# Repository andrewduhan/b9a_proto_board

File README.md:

# B9A Proto Board
Prototyping board for vacuum tubes that use a B9A socket

Board measures 3.95" x 3.15"

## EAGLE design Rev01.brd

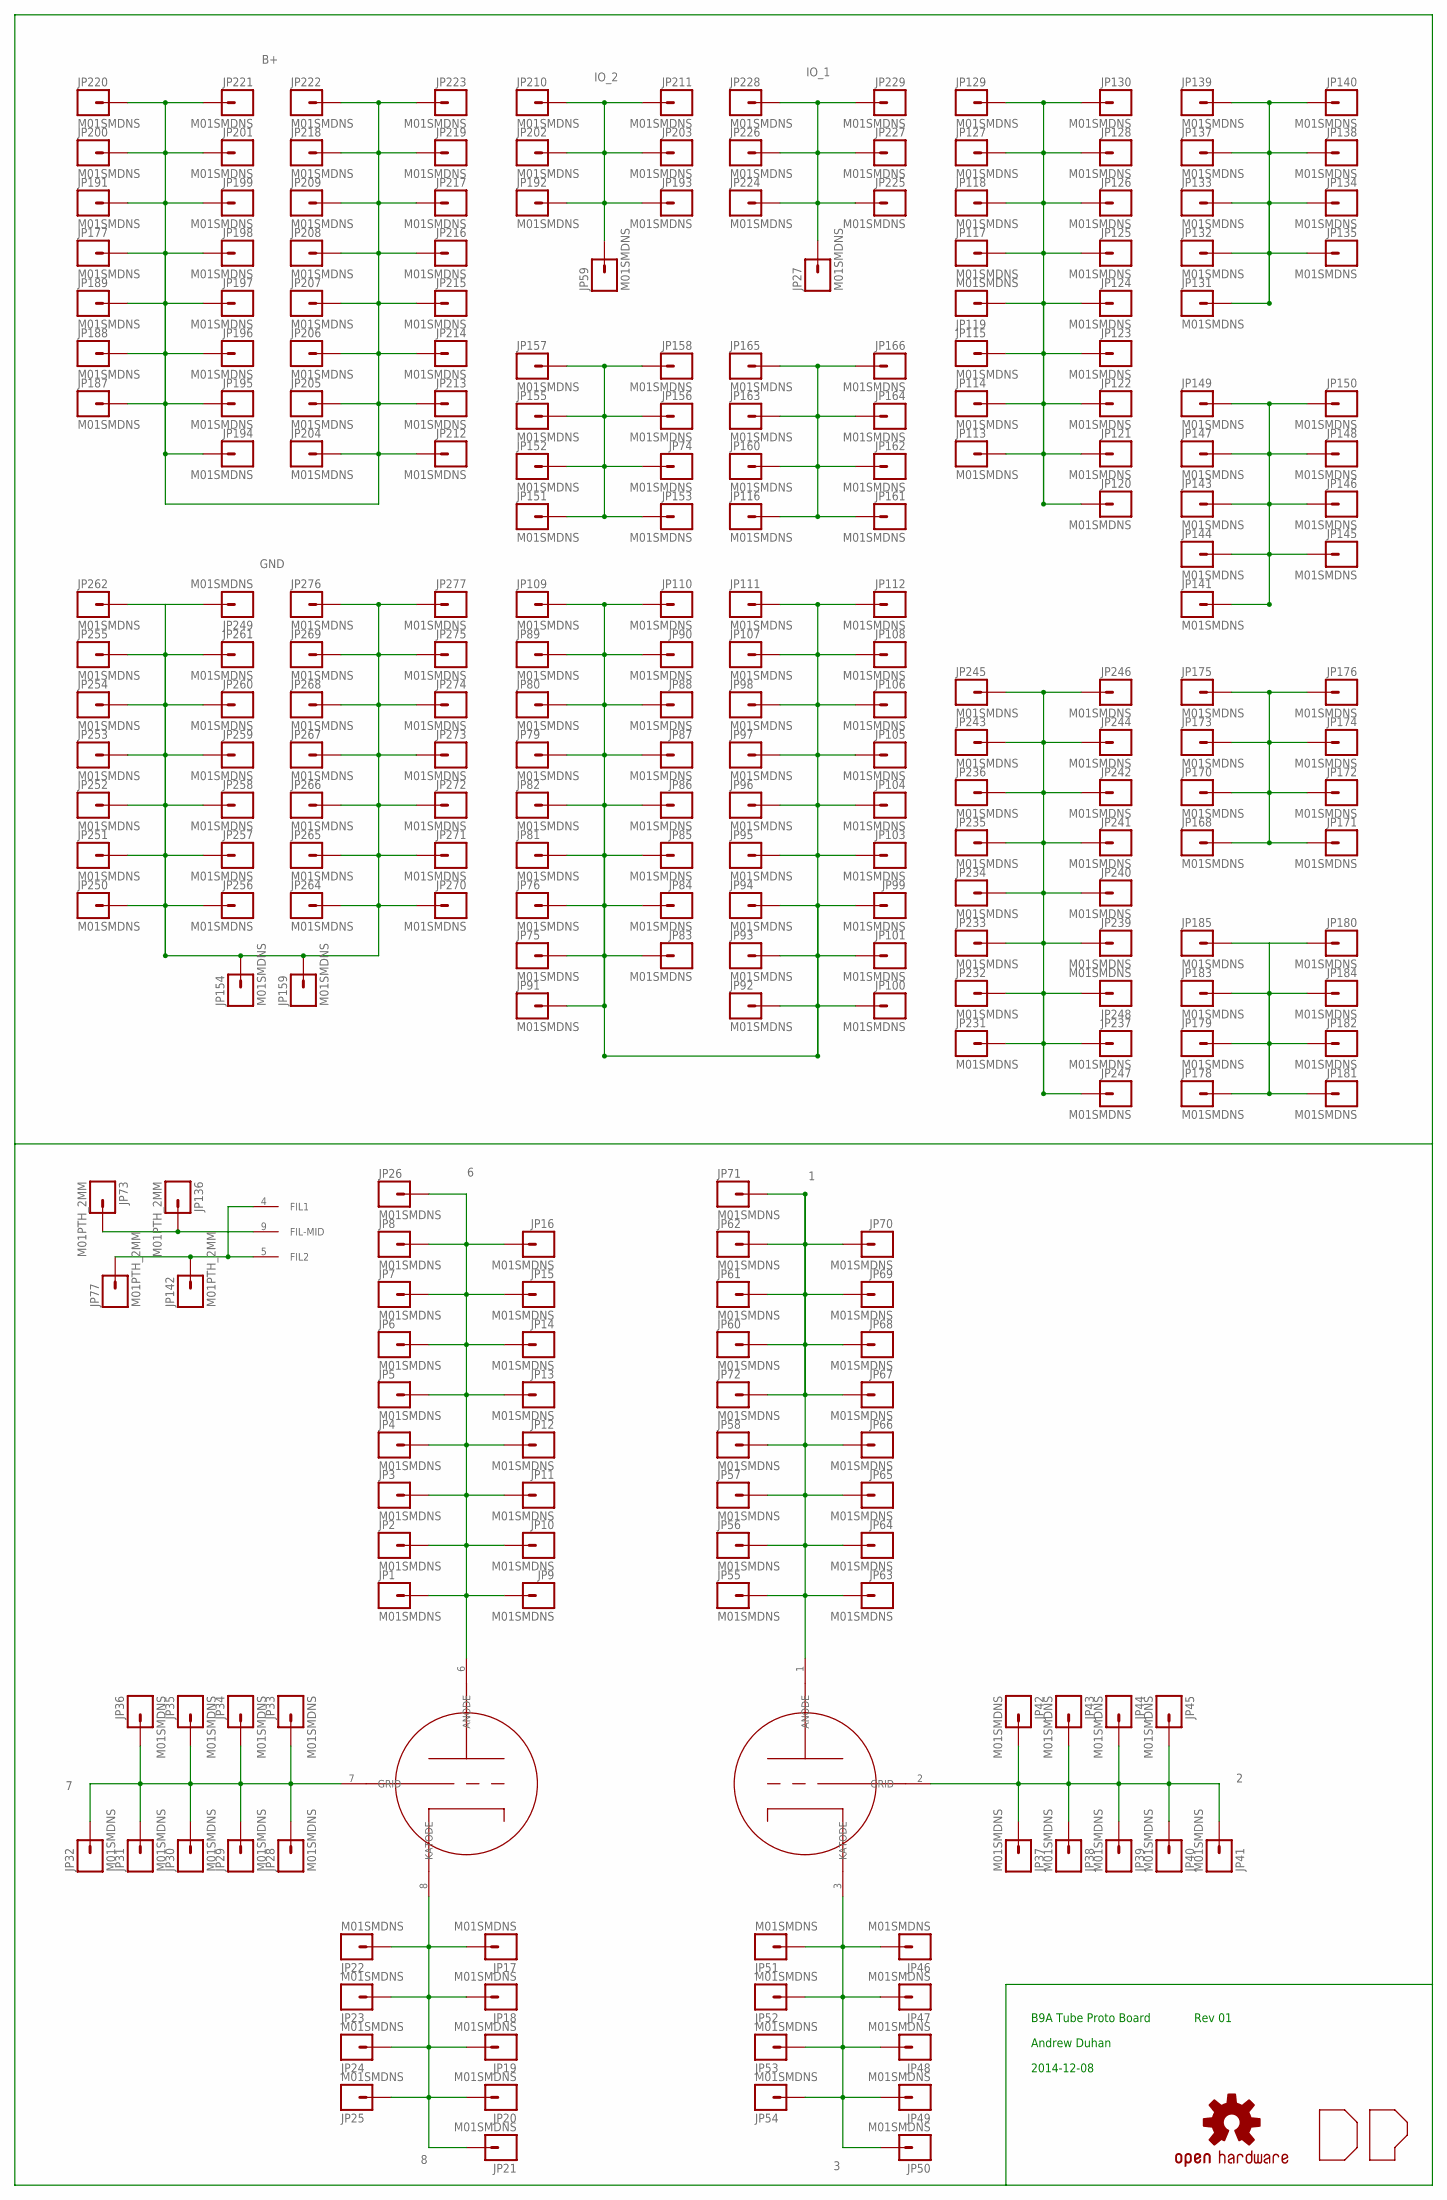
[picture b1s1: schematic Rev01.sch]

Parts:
JP1, JP2, JP3, JP4, JP5, JP6, JP7, JP8, JP9, JP10, JP11, JP12, JP13, JP14, JP15, JP16, JP17, JP18, JP19, JP20, JP21, JP22, JP23, JP24, JP25, JP26, JP27, JP28, JP29, JP30, JP31, JP32, JP33, JP34, JP35, JP36, JP37, JP38, JP39, JP40, JP41, JP42, JP43, JP44, JP45, JP46, JP47, JP48, JP49, JP50, JP51, JP52, JP53, JP54, JP55, JP56, JP57, JP58, JP59, JP60, JP61, JP62, JP63, JP64, JP65, JP66, JP67, JP68, JP69, JP70, JP71, JP72, JP74, JP75, JP76, JP79, JP80, JP81, JP82, JP83, JP84, JP85, JP86, JP87, JP88, JP89, JP90, JP91, JP92, JP93, JP94, JP95, JP96, JP97, JP98, JP99, JP100, JP101, JP103, JP104, JP105, JP106, JP107, JP108, JP109, JP110, JP111, JP112, JP113, JP114, JP115, JP116, JP117, JP118, JP119, JP120, JP121, JP122, JP123, JP124, JP125, JP126, JP127, JP128, JP129, JP130, JP131, JP132, JP133, JP134, JP135, JP137, JP138, JP139, JP140, JP141, JP143, JP144, JP145, JP146, JP147, JP148, JP149, JP150, JP151, JP152, JP153, JP154, JP155, JP156, JP157, JP158, JP159, JP160, JP161, JP162, JP163, JP164, JP165, JP166, JP168, JP170, JP171, JP172, JP173, JP174, JP175, JP176, JP177, JP178, JP179, JP180, JP181, JP182, JP183, JP184, JP185, JP187, JP188, JP189, JP191, JP192, JP193, JP194, JP195, JP196, JP197, JP198, JP199, JP200, JP201, JP202, JP203, JP204, JP205, JP206, JP207, JP208, JP209, JP210, JP211, JP212, JP213, JP214, JP215, JP216, JP217, JP218, JP219, JP220, JP221, JP222, JP223, JP224, JP225, JP226, JP227, JP228, JP229, JP231, JP232, JP233, JP234, JP235, JP236, JP237, JP239, JP240, JP241, JP242, JP243, JP244, JP245, JP246, JP247, JP248, JP249, JP250, JP251, JP252, JP253, JP254, JP255, JP256, JP257, JP258, JP259, JP260, JP261, JP262, JP264, JP265, JP266, JP267, JP268, JP269, JP270, JP271, JP272, JP273, JP274, JP275, JP276, JP277: M01SMDNS; 1X01NS
JP73, JP77, JP136, JP142: M01PTH_2MM; 1X01_2MM
LOGO1: OSHW-LOGOM; OSHW-LOGO-M
U$1: 12AX7; 12AX7-ROUND
U$2: DP_LOGO

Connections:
1: JP55.1, JP56.1, JP57.1, JP58.1, JP60.1, JP61.1, JP62.1, JP63.1, JP64.1, JP65.1, JP66.1, JP67.1, JP68.1, JP69.1, JP70.1, JP71.1, JP72.1, U$1.1 (ANODE)
2: JP37.1, JP38.1, JP39.1, JP40.1, JP41.1, JP42.1, JP43.1, JP44.1, JP45.1, U$1.2 (GRID)
3: JP46.1, JP47.1, JP48.1, JP49.1, JP50.1, JP51.1, JP52.1, JP53.1, JP54.1, U$1.3 (KATODE)
4/5: JP77.1, JP142.1, U$1.4 (FIL1), U$1.5 (FIL2)
6: JP1.1, JP2.1, JP3.1, JP4.1, JP5.1, JP6.1, JP7.1, JP8.1, JP9.1, JP10.1, JP11.1, JP12.1, JP13.1, JP14.1, JP15.1, JP16.1, JP26.1, U$1.6 (ANODE)
7: JP28.1, JP29.1, JP30.1, JP31.1, JP32.1, JP33.1, JP34.1, JP35.1, JP36.1, U$1.7 (GRID)
8: JP17.1, JP18.1, JP19.1, JP20.1, JP21.1, JP22.1, JP23.1, JP24.1, JP25.1, U$1.8 (KATODE)
9: JP73.1, JP136.1, U$1.9 (FIL-MID)
B+: JP177.1, JP187.1, JP188.1, JP189.1, JP191.1, JP194.1, JP195.1, JP196.1, JP197.1, JP198.1, JP199.1, JP200.1, JP201.1, JP204.1, JP205.1, JP206.1, JP207.1, JP208.1, JP209.1, JP212.1, JP213.1, JP214.1, JP215.1, JP216.1, JP217.1, JP218.1, JP219.1, JP220.1, JP221.1, JP222.1, JP223.1
GND: JP154.1, JP159.1, JP249.1, JP250.1, JP251.1, JP252.1, JP253.1, JP254.1, JP255.1, JP256.1, JP257.1, JP258.1, JP259.1, JP260.1, JP261.1, JP262.1, JP264.1, JP265.1, JP266.1, JP267.1, JP268.1, JP269.1, JP270.1, JP271.1, JP272.1, JP273.1, JP274.1, JP275.1, JP276.1, JP277.1
IO_1: JP27.1, JP224.1, JP225.1, JP226.1, JP227.1, JP228.1, JP229.1
IO_2: JP59.1, JP192.1, JP193.1, JP202.1, JP203.1, JP210.1, JP211.1
unnamed: JP75.1, JP76.1, JP79.1, JP80.1, JP81.1, JP82.1, JP83.1, JP84.1, JP85.1, JP86.1, JP87.1, JP88.1, JP89.1, JP90.1, JP91.1, JP92.1, JP93.1, JP94.1, JP95.1, JP96.1, JP97.1, JP98.1, JP99.1, JP100.1, JP101.1, JP103.1, JP104.1, JP105.1, JP106.1, JP107.1, JP108.1, JP109.1, JP110.1, JP111.1, JP112.1
unnamed: JP113.1, JP114.1, JP115.1, JP117.1, JP118.1, JP119.1, JP120.1, JP121.1, JP122.1, JP123.1, JP124.1, JP125.1, JP126.1, JP127.1, JP128.1, JP129.1, JP130.1
unnamed: JP131.1, JP132.1, JP133.1, JP134.1, JP135.1, JP137.1, JP138.1, JP139.1, JP140.1
unnamed: JP141.1, JP143.1, JP144.1, JP145.1, JP146.1, JP147.1, JP148.1, JP149.1, JP150.1
unnamed: JP74.1, JP151.1, JP152.1, JP153.1, JP155.1, JP156.1, JP157.1, JP158.1
unnamed: JP116.1, JP160.1, JP161.1, JP162.1, JP163.1, JP164.1, JP165.1, JP166.1
unnamed: JP168.1, JP170.1, JP171.1, JP172.1, JP173.1, JP174.1, JP175.1, JP176.1
unnamed: JP178.1, JP179.1, JP180.1, JP181.1, JP182.1, JP183.1, JP184.1, JP185.1
unnamed: JP231.1, JP232.1, JP233.1, JP234.1, JP235.1, JP236.1, JP237.1, JP239.1, JP240.1, JP241.1, JP242.1, JP243.1, JP244.1, JP245.1, JP246.1, JP247.1, JP248.1

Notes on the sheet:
B9A Tube Proto Board
Andrew Duhan
2014-12-08
Rev 01

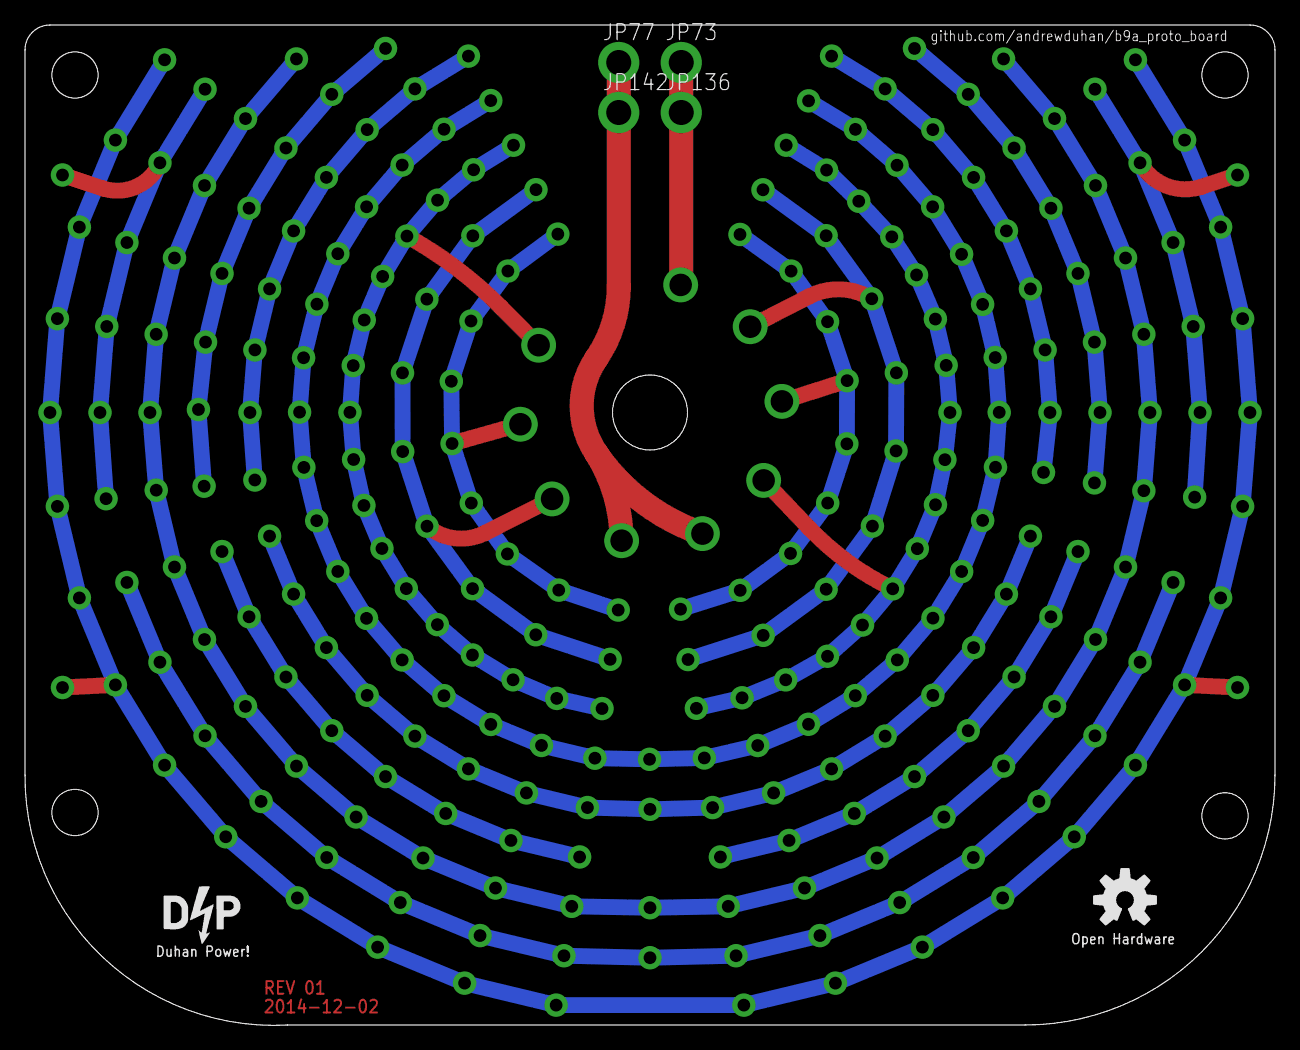
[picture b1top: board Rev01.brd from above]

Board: 2 copper layers, 100.0 x 80.0 mm, 271 parts (1 on the bottom side), 21 nets.

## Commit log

2017-06-20 Rev 01

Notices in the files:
parts and their libraries:
SparkFun-Connectors: Licensing: CC v3.0 Share-Alike You are welcome to use this library for commercial purposes.
